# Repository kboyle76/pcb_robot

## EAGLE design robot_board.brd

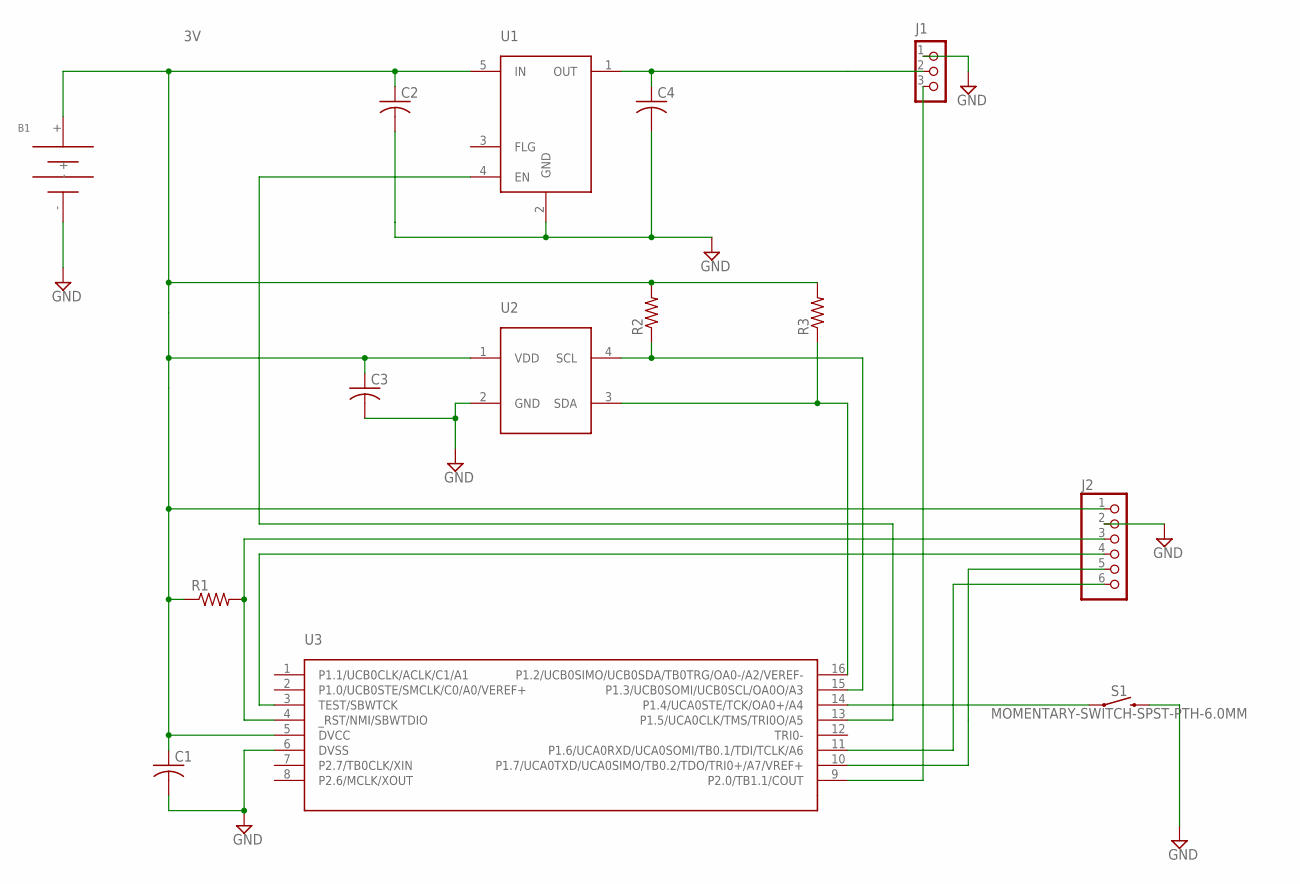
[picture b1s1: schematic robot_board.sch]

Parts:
B1: 2XAAA_HOLDER; CHEAP_ASS_CHINESE_BH
C1, C2, C3, C4: C-USC0805; C0805
J1: CON_HEADER_1X03-PTH_RIGHT_ANGLED; M1X3_MALE_RIGHT_ANGLED
J2: PINHD-1X6; 1X06
R1, R2, R3: R-US_R0805; R0805
S1: MOMENTARY-SWITCH-SPST-PTH-6.0MM; TACTILE_SWITCH_PTH_6.0MM
U1: DI_AP22802AW5-7; SOT-25
U2: LITE-ON_LTR-329ALS-01
U3: TI_MSP430FR2310IPW16R; PW_R-PDSO-G16

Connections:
3V: B1.+, C1.1, C2.1, C3.1, J2.1, R1.1, R2.2, R3.2, U1.5 (IN), U2.1 (VDD), U3.5 (DVCC)
GND: B1.-, C1.2, C2.2, C3.2, C4.2, J1.1, J2.2, S1.3 (2), U1.2 (GND), U2.2 (GND), U3.6 (DVSS)
unnamed: U1.4 (EN), U3.13 (P1.5/UCA0CLK/TMS/TRI0O/A5)
unnamed: R2.1, U2.4 (SCL), U3.15 (P1.3/UCB0SOMI/UCB0SCL/OA0O/A3)
unnamed: R3.1, U2.3 (SDA), U3.16 (P1.2/UCB0SIMO/UCB0SDA/TB0TRG/OA0-/A2/VE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)
unnamed: C4.1, J1.2, U1.1 (OUT)
unnamed: J2.3, R1.2, U3.4 (_RST/NMI/SBWTDIO)
unnamed: J1.3, U3.9 (P2.0/TB1.1/COUT)
unnamed: J2.4, U3.3 (TEST/SBWTCK)
unnamed: J2.6, U3.11 (P1.6/UCA0RXD/UCA0SOMI/TB0.1/TDI/TCLK/A6)
unnamed: J2.5, U3.10 (P1.7/UCA0TXD/UCA0SIMO/TB0.2/TDO/TRI0+/A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)
unnamed: S1.1, U3.14 (P1.4/UCA0STE/TCK/OA0+/A4)

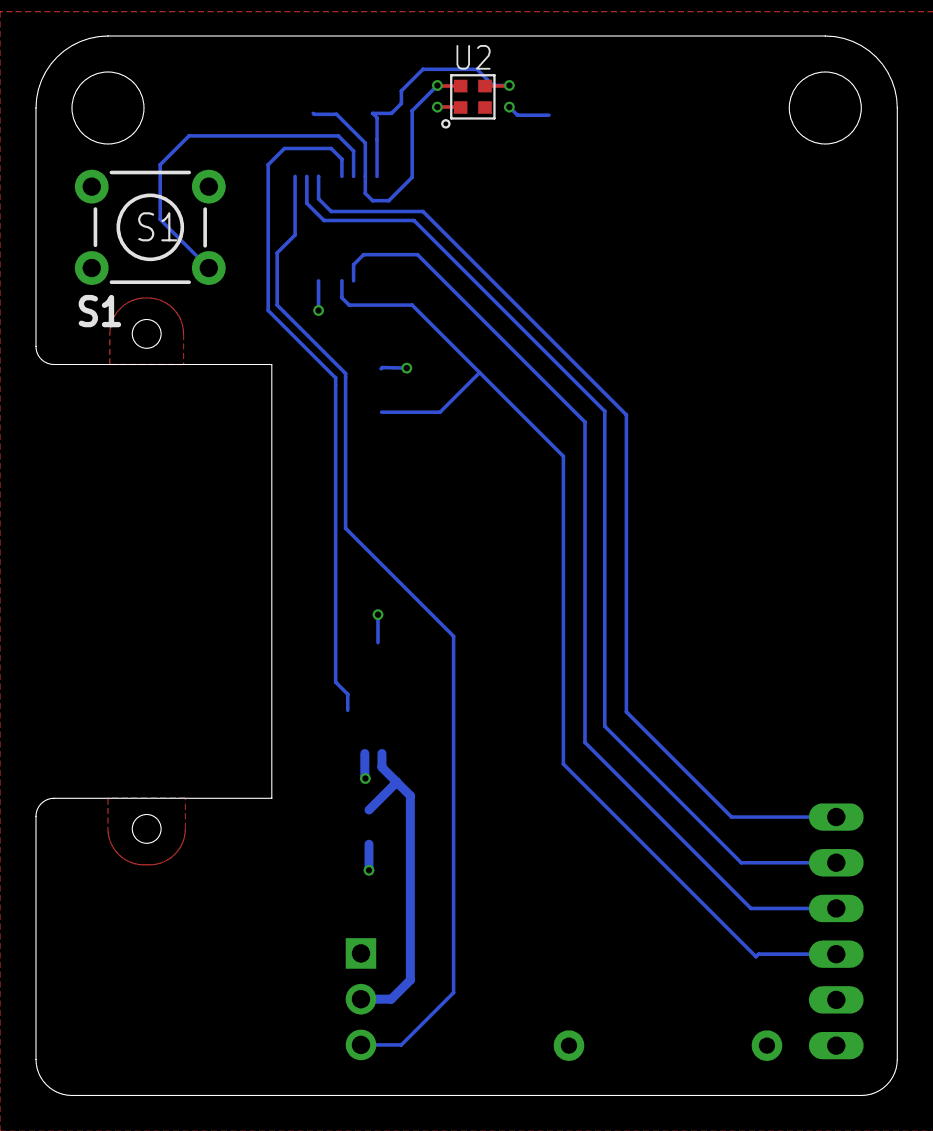
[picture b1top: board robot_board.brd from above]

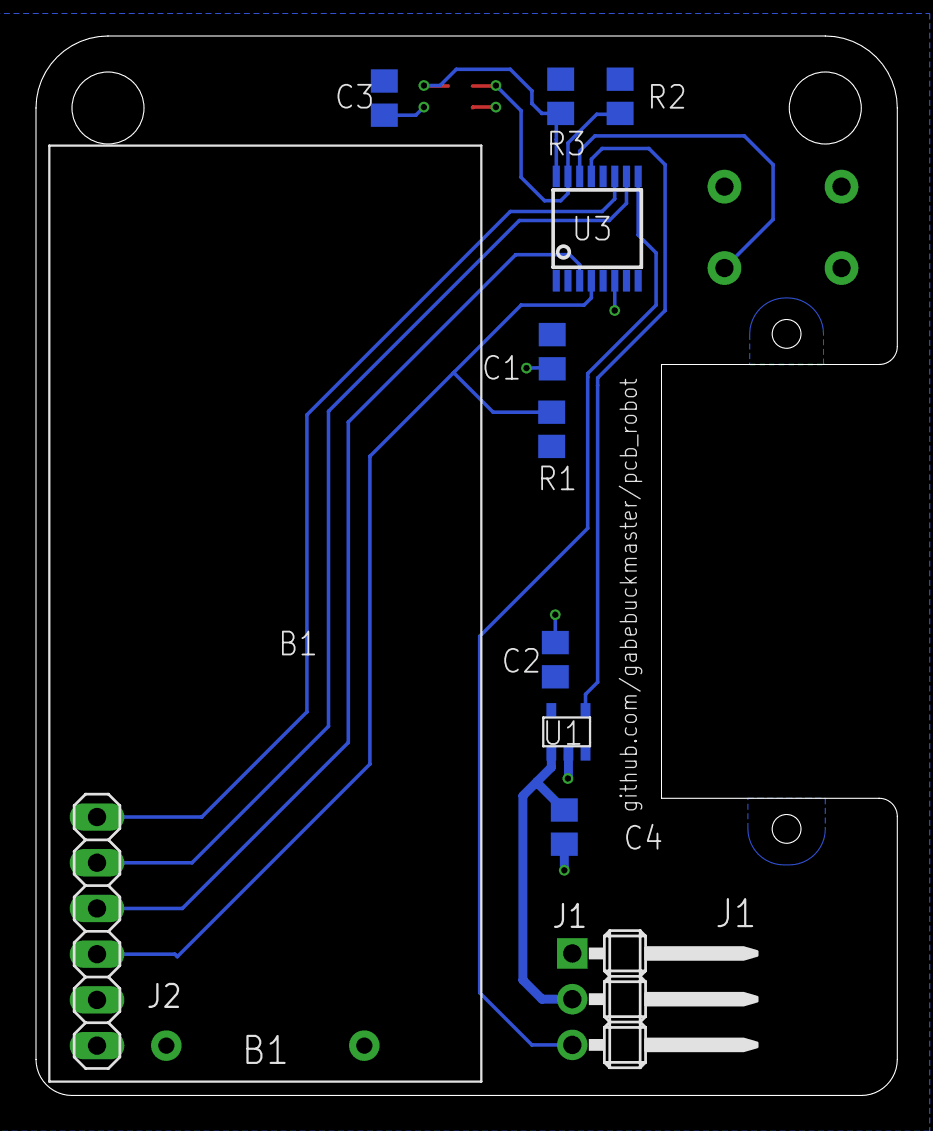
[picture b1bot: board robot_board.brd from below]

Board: 2 copper layers, 47.9 x 58.9 mm, 14 parts (12 on the bottom side), 12 nets.

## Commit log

2020-03-16 Raw project files
